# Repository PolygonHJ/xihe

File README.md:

# Xihe
**Xihe** is a self-sustaining, ultra-low-power sensing platform designed for long-lifetime deployments with zero maintenance. Powered by ambient energy sources such as solar or background RF, the system stores energy in supercapacitors until it reaches a threshold sufficient to activate, sense, and transmit data wirelessly. Once depleted, it enters a dormant state and repeats the cycle.

The system is designed to be as small and unobtrusive as possible, enabling it to be placed in an environment, monitor passively, and be forgotten—both visually and in terms of maintenance.

## System Overview
The platform consists of:

### 1. **Main Board — "Xihe-Core"**
- Hosts the energy harvesting and power management circuitry,
- Includes high-capacitance supercapacitor storage,
- Integrates a **Seeed XIAO nRF54L15** module for BLE/Zigbee communication,
- Provides a modular connector interface for sensor boards (I²C, SPI, UART, Analogue),
- Manages energy thresholds and system wakeup logic.

### 2. **Sensor Modules**
- Plug-in sensor boards for flexibility,
- Operate only during active energy windows to minimize load,
- Interchangeable to allow flexibility in deployment.

### 3. **Energy Storage Modules**
- Optional add-ons for extended runtime or energy reserve (Supercapacitors or Batteries),
- Connect to the side or bottom of the board for flexibility,
- Extend active life at the cost of increased physical size.

## Features
- ⚡ **Ambient Energy Harvesting**: Solar (single-cell) supported; RF harvesting planned,
- 🔋 **Supercapacitor-Based Power Storage**: Maintenance-free,
- 📡 **Low-Power Wireless Comms**: BLE/Zigbee-ready for periodic broadcast,
- 🧩 **Modular Sensing**: Swappable sensor boards and energy modules for application-specific deployments,
- 🔄 **Cyclic Operation**: Charge → Activate → Sense → Transmit → Sleep,
- ♻️ **Designed for Longevity**: No batteries, no wires, no maintenance

## Use Cases
The project is intended for low-effort, low-maintenance monitoring in home automation or other low-frequency sensing environments.

Example sensing applications:
- Light  
- Temperature  
- Humidity  
- Moisture  
- Open/Close (e.g. reed switch)  

## Status
The hardware is under active development. No hardware for software has been produced or tested yet.

# Future Ideas
- Energy storage modules,
- RF energy harvesting,
- Modularise harvesting and energy storage sections.

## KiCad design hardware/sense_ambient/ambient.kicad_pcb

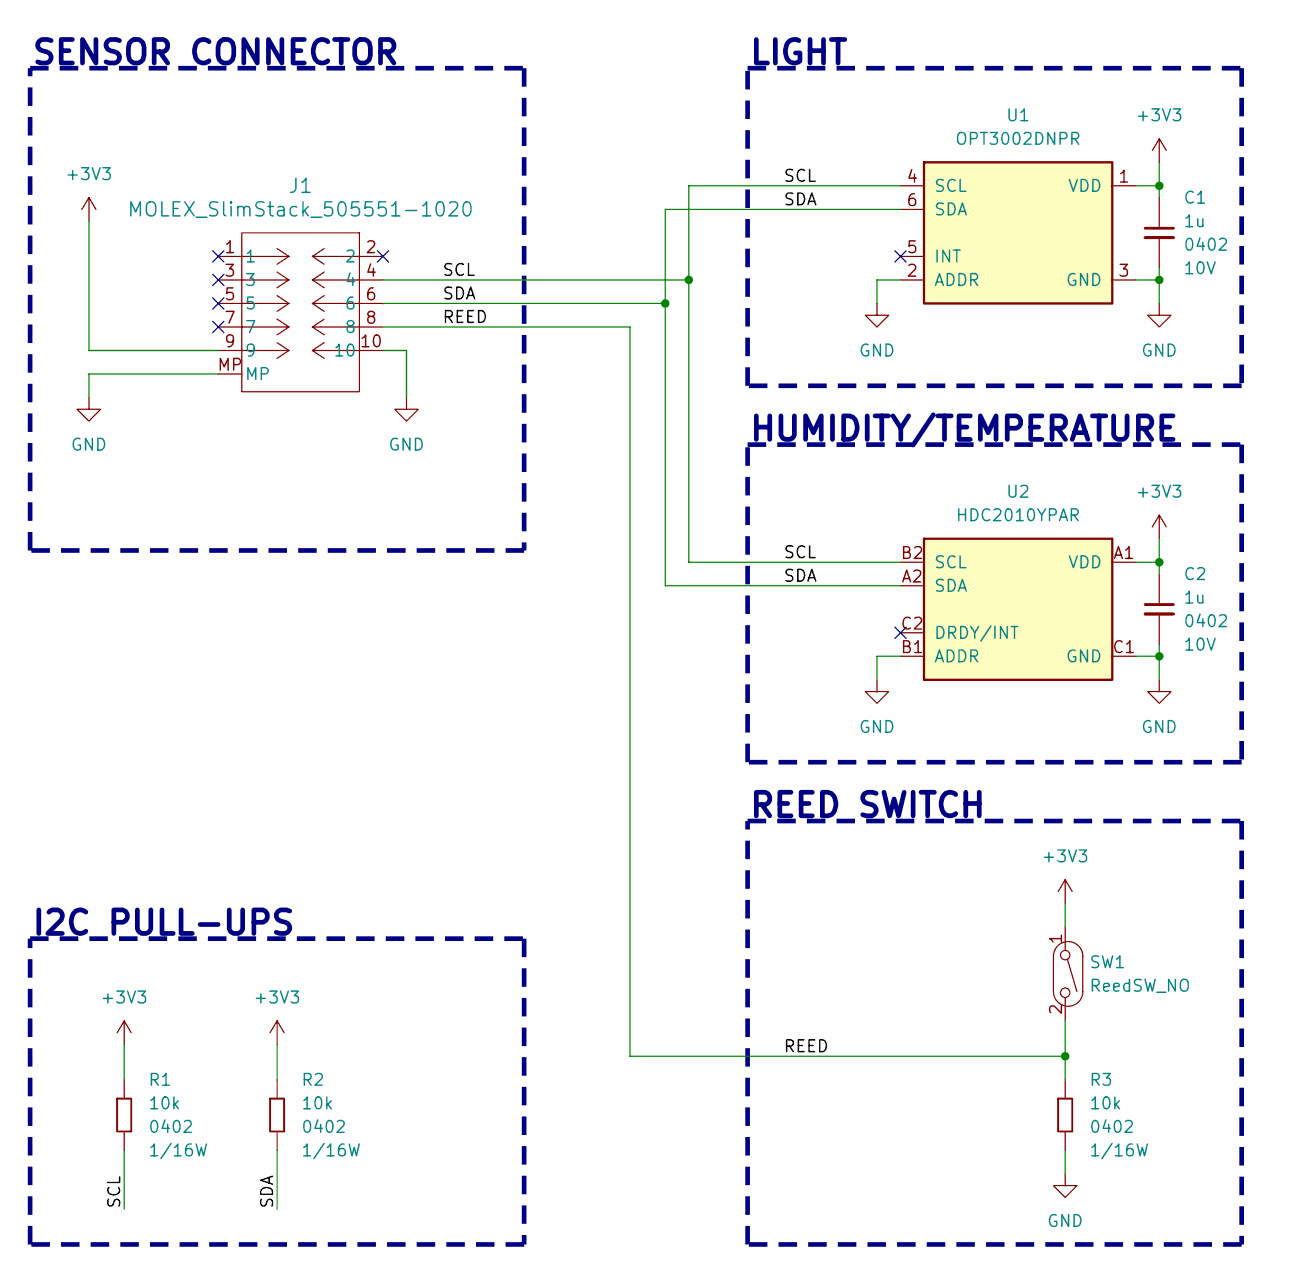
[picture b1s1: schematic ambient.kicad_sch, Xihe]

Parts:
C1, C2: 1u; C_0402_1005Metric; Voltage Rating 10V; Part Number GRM155Z71A105KE01J
J1: MOLEX_SlimStack_505551-1020; Part Number 5055511020
R1, R2, R3: 10k; R_0402_1005Metric; Part Number RC0402FR-0710KP
SW1: ReedSW_NO; COMUS_RI80SMDM0510J1; Part Number RI80SMDM-0510-J1
U1: OPT3002DNPR; TI_6USON_DNP; Part Number OPT3002DNPR
U2: HDC2010YPAR; TI_6DSBGA_YPA; Part Number HDC2010YPAR

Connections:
+3V3: C1.1, C2.1, J1.9, R1.1, R2.1, SW1.1 (A), U1.1 (VDD), U2.A1 (VDD)
/REED: J1.8, R3.1, SW1.2 (B)
/SCL: J1.4, R1.2, U1.4 (SCL), U2.B2 (SCL)
/SDA: J1.6, R2.2, U1.6 (SDA), U2.A2 (SDA)
GND: C1.2, C2.2, J1.10, J1.MP, R3.2, U1.2 (ADDR), U1.3 (GND), U1.7 (GND), U2.B1 (ADDR), U2.C1 (GND)

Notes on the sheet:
REED SWITCH
SENSOR CONNECTOR
I2C PULL-UPS
HUMIDITY/TEMPERATURE
LIGHT

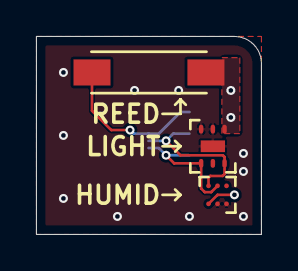
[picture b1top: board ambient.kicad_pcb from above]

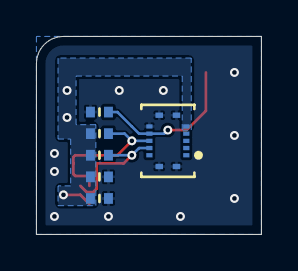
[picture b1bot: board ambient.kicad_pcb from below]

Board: 2 copper layers, 12.5 x 11.0 mm, 9 parts (6 on the bottom side), 5 nets.

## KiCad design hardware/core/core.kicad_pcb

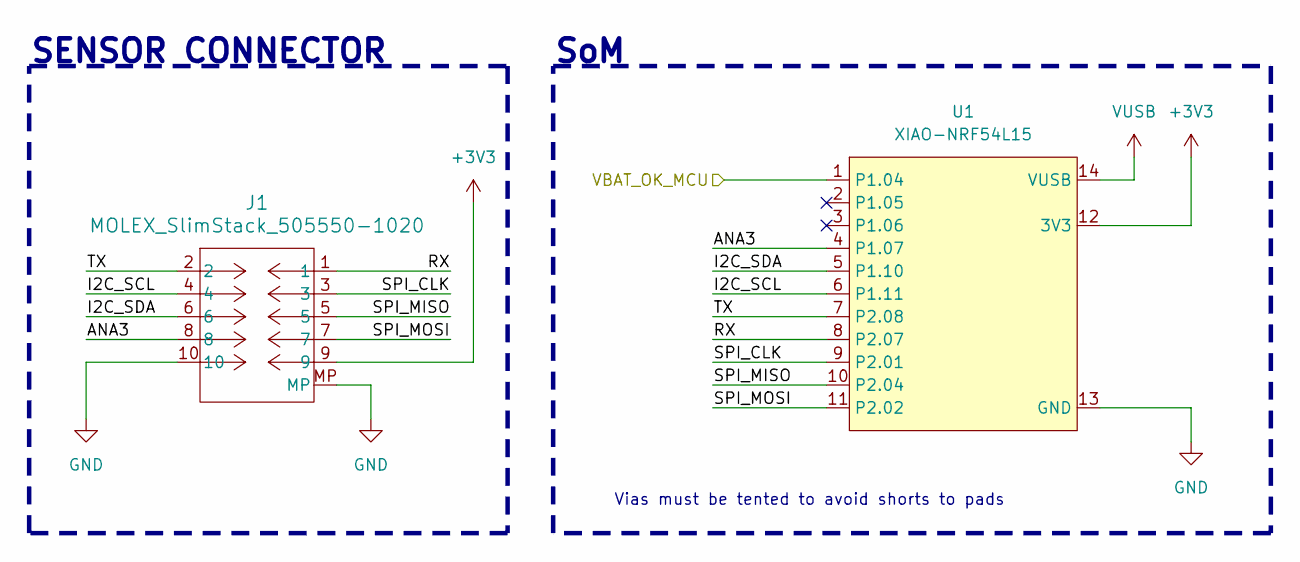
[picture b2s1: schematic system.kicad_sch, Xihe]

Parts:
J1: MOLEX_SlimStack_505550-1020; Part Number 5055501020
U1: XIAO-NRF54L15; XIAO-NRF54L15-DIP; Part Number XIAO-NRF54L15

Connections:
+3V3: J1.9, U1.12 (3V3); also elsewhere on the board
/harvester/VBAT_OK_MCU: U1.1 (P1.04); also elsewhere on the board
/system/ANA3: J1.8, U1.4 (P1.07)
/system/I2C_SCL: J1.4, U1.6 (P1.11)
/system/I2C_SDA: J1.6, U1.5 (P1.10)
/system/RX: J1.1, U1.8 (P2.07)
/system/SPI_CLK: J1.3, U1.9 (P2.01)
/system/SPI_MISO: J1.5, U1.10 (P2.04)
/system/SPI_MOSI: J1.7, U1.11 (P2.02)
/system/TX: J1.2, U1.7 (P2.08)
GND: J1.10, J1.MP, U1.13 (GND); also elsewhere on the board
VUSB: U1.14 (VUSB); also elsewhere on the board

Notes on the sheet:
SoM
SENSOR CONNECTOR
Vias must be tented to avoid shorts to pads

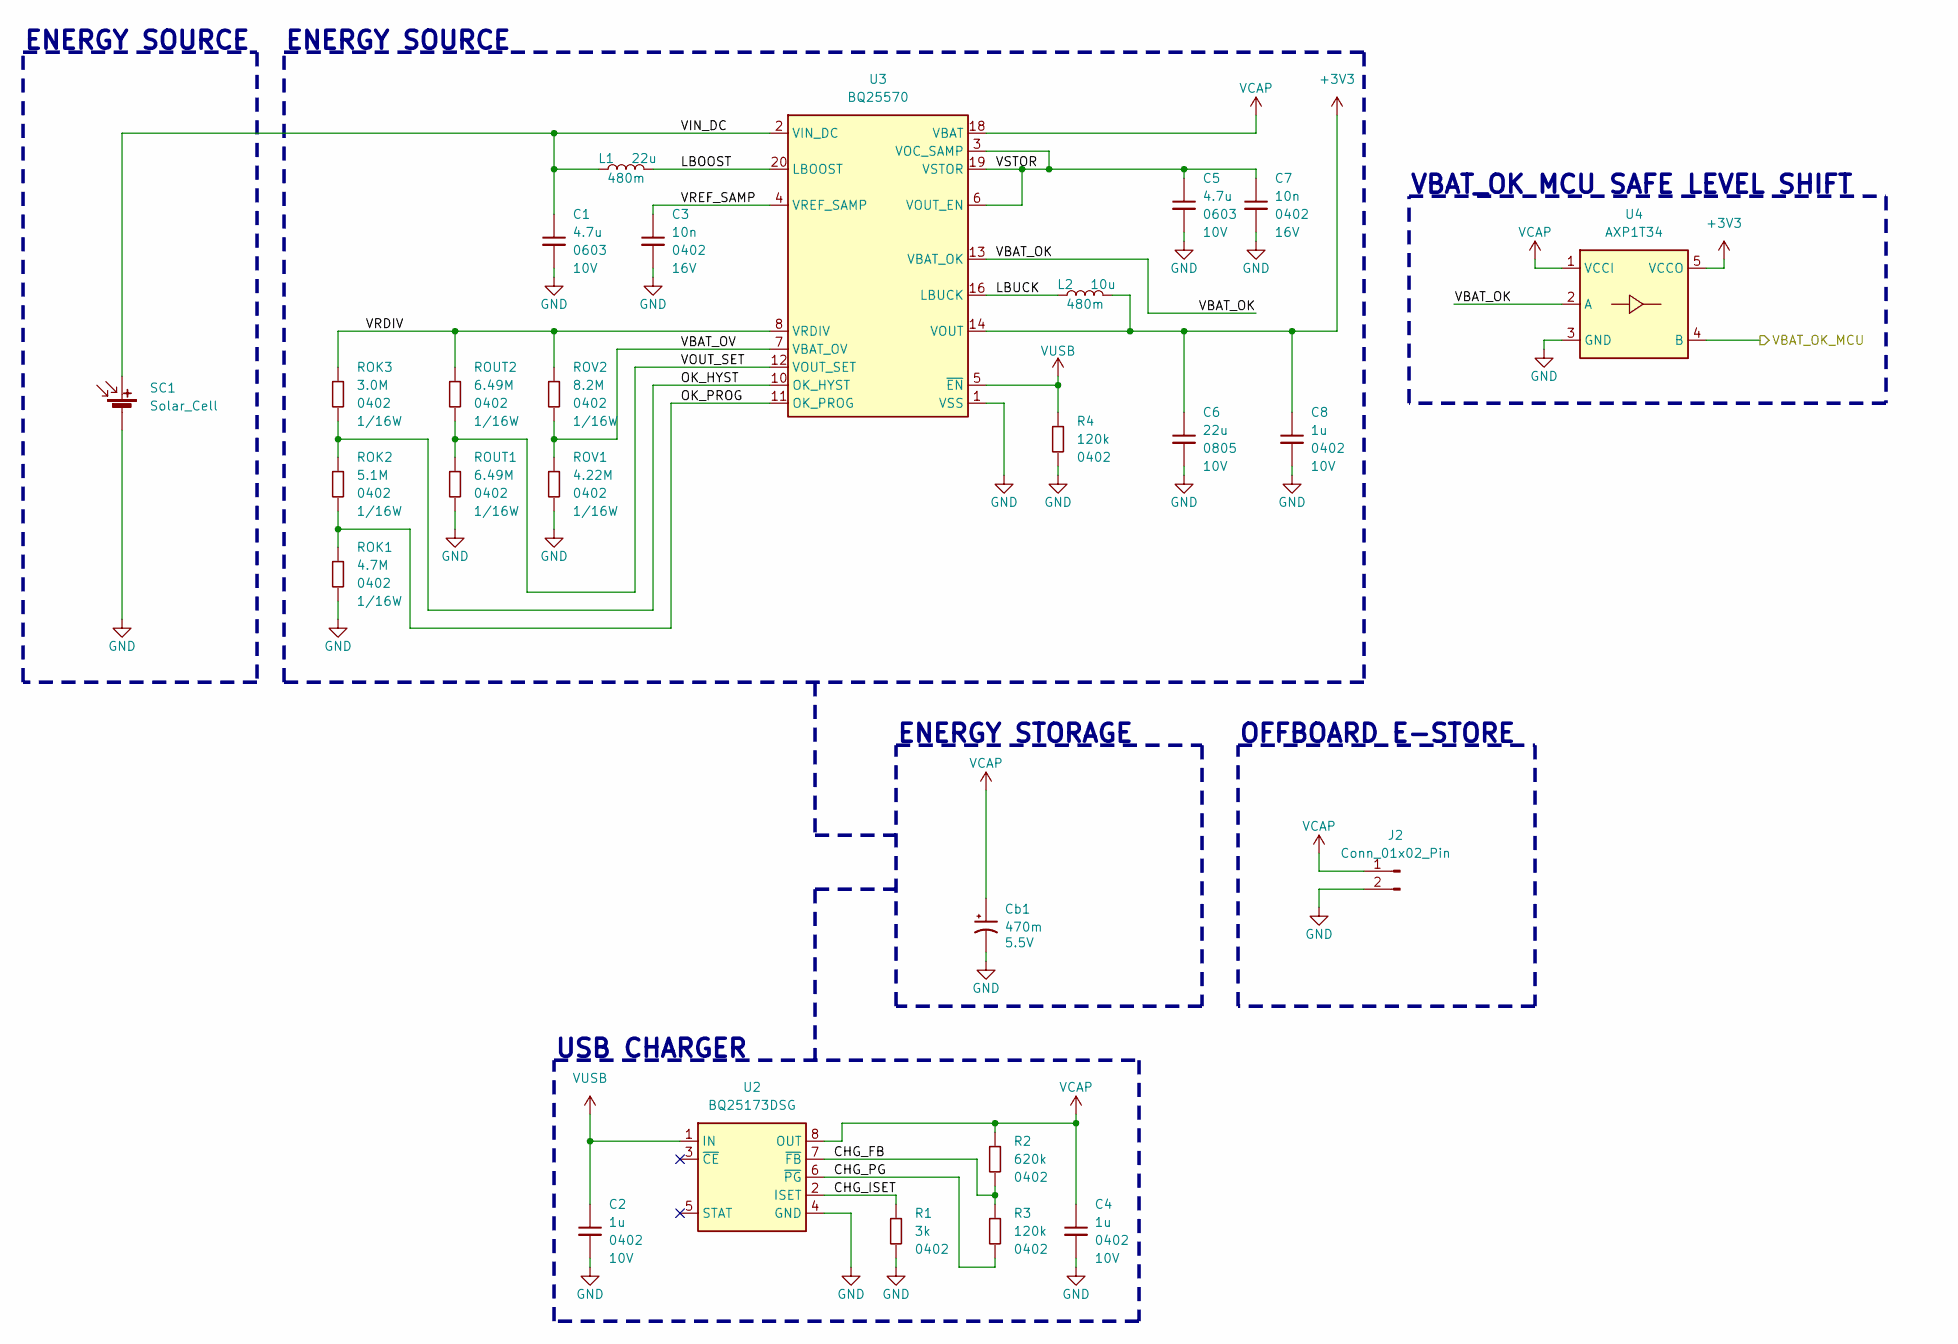
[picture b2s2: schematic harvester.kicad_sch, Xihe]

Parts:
C1, C5: 4.7u; C_0603_1608Metric; Voltage Rating 10V; Part Number GRM188Z71A475ME15D
C2, C4, C8: 1u; C_0402_1005Metric; Voltage Rating 10V; Part Number GRM155Z71A105KE01J
C3, C7: 10n; C_0402_1005Metric; Voltage Rating 16V; Part Number GRM155R71C103KA01D
C6: 22u; C_0805_2012Metric; Voltage Rating 10V; Part Number GRM21BZ71A226ME15L
Cb1: 470m; EATON_KR5R5H474R; Voltage Rating 5.5V; Part Number EDC474Z5R5H
J2: Conn_01x02_Pin; PD_801-83-002-20-001101; Part Number 801-83-002-20-001101
L1: 22u; TY_Inductor_NRS4012; Part Number NRS4012T220MDGJ
L2: 10u; L_1008_2520Metric; Part Number DFE252012F-100M=P2
R1: 3k; R_0402_1005Metric; Part Number RC0402FR-133KL
R2: 620k; R_0402_1005Metric; Part Number RC0402FR-07620KL
R3, R4: 120k; R_0402_1005Metric; Part Number RC0402FR-07120KL
ROK1: 4.7M; R_0402_1005Metric; Part Number RC0402FR-074M7L
ROK2: 5.1M; R_0402_1005Metric; Part Number RC0402FR-075M1L
ROK3: 3.0M; R_0402_1005Metric; Part Number RC0402FR-073ML
ROUT1, ROUT2: 6.49M; R_0402_1005Metric; Part Number RC0402FR-076M49L
ROV1: 4.22M; R_0402_1005Metric; Part Number RC0402FR-074M22L
ROV2: 8.2M; R_0402_1005Metric; Part Number RC0402FR-078M2L
SC1: Solar_Cell; ANYSOLAR_KXOB25; Part Number KXOB25-03X4F-TR
U2: BQ25173DSG; TI_8WSON_DSG; Part Number BQ25173DSGR
U3: BQ25570; TI_20VQFN_RGR; Part Number BQ25570RGRR
U4: AXP1T34; NX_5SOT353; Part Number 74AXP1T34GWH

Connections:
+3V3: C6.1, C8.1, L2.2, U3.14 (VOUT), U4.5 (VCCO); also elsewhere on the board
/harvester/CHG_FB: R2.2, R3.1, U2.7 (~FB)
/harvester/CHG_ISET: R1.1, U2.2 (ISET)
/harvester/CHG_PG: R3.2, U2.6 (~PG)
/harvester/LBOOST: L1.2, U3.20 (LBOOST)
/harvester/LBUCK: L2.1, U3.16 (LBUCK)
/harvester/OK_HYST: ROK2.1, ROK3.2, U3.10 (OK_HYST)
/harvester/OK_PROG: ROK1.1, ROK2.2, U3.11 (OK_PROG)
/harvester/VBAT_OK: U3.13 (VBAT_OK), U4.2 (A)
/harvester/VBAT_OK_MCU: U4.4 (B); also elsewhere on the board
/harvester/VBAT_OV: ROV1.1, ROV2.2, U3.7 (VBAT_OV)
/harvester/VIN_DC: C1.1, L1.1, SC1.1 (+), U3.2 (VIN_DC)
/harvester/VOUT_SET: ROUT1.1, ROUT2.2, U3.12 (VOUT_SET)
/harvester/VRDIV: ROK3.1, ROUT2.1, ROV2.1, U3.8 (VRDIV)
/harvester/VREF_SAMP: C3.1, U3.4 (VREF_SAMP)
/harvester/VSTOR: C5.1, C7.1, U3.3 (VOC_SAMP), U3.6 (VOUT_EN), U3.19 (VSTOR)
GND: C1.2, C2.2, C3.2, C4.2, C5.2, C6.2, C7.2, C8.2, Cb1.2, J2.2, R1.2, R4.2, ROK1.2, ROUT1.2, ROV1.2, SC1.2 (-), U2.4 (GND), U2.9 (GND), U3.1 (VSS), U3.9 (VSS), U3.15 (VSS), U3.17 (VSS), U3.21 (VSS), U4.3 (GND); also elsewhere on the board
VCAP: C4.1, Cb1.1, J2.1, R2.1, U2.8 (OUT), U3.18 (VBAT), U4.1 (VCCI)
VUSB: C2.1, R4.1, U2.1 (IN), U3.5 (~EN); also elsewhere on the board

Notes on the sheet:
VBAT_OK MCU SAFE LEVEL SHIFT
ENERGY STORAGE
OFFBOARD E-STORE
ENERGY SOURCE
USB CHARGER

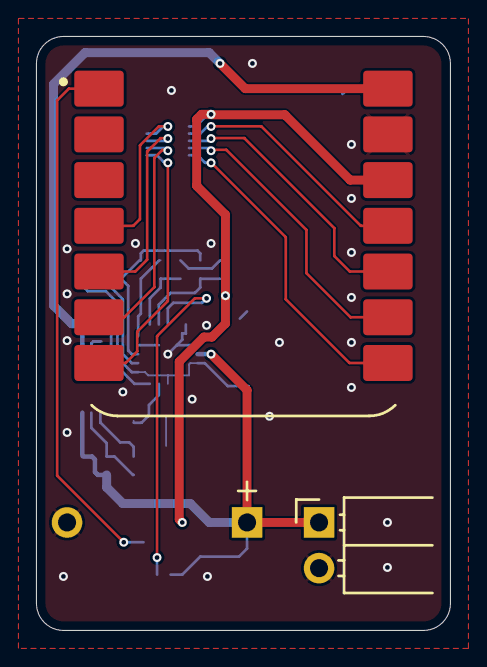
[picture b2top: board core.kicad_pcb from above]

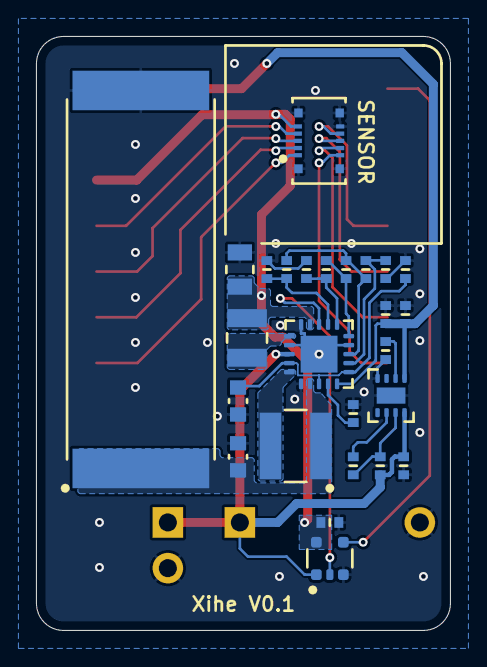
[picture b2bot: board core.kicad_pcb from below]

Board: 2 copper layers, 23.0 x 33.0 mm, 29 parts (26 on the bottom side), 27 nets.

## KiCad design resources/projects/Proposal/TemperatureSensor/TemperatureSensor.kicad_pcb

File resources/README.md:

# Resources

- [Energy Harvester](./energy_harvester/): files related to the energy harvester chip (such as calculations).
- [PcbWay Manufacturing Files](./pcbway_manufacturing_rules/): reference rules file with PcbWays manufacturing capabilities.
- [Projects](./projects/): reference projects and exmaples;
  - [Proposal](./projects/Proposal/) is an initial concept design for a single sided board to test hardware with. This primarily was to test the USB-SWD circuit more easily, but the replacement on this sub-circuit with the Xiao nRF54L15 means the test design is less required.
  - [Xiao nRF54L15 Module](https://wiki.seeedstudio.com/xiao_nrf54l15_sense_getting_started/), an nRF54L15 module from seeed studio used for this project.
  - [BeeLight](https://github.com/Kampi/BeeLight), open source zigbee environment sensor.
  - [Pi Debug Probe](./projects/Pi%20Debugger), onboard USB-SWD schematics and firmware. 
  - [Solar nRF](https://github.com/PocketConcepts/Solar_nRF), low energy harvester example using the BQ25504.

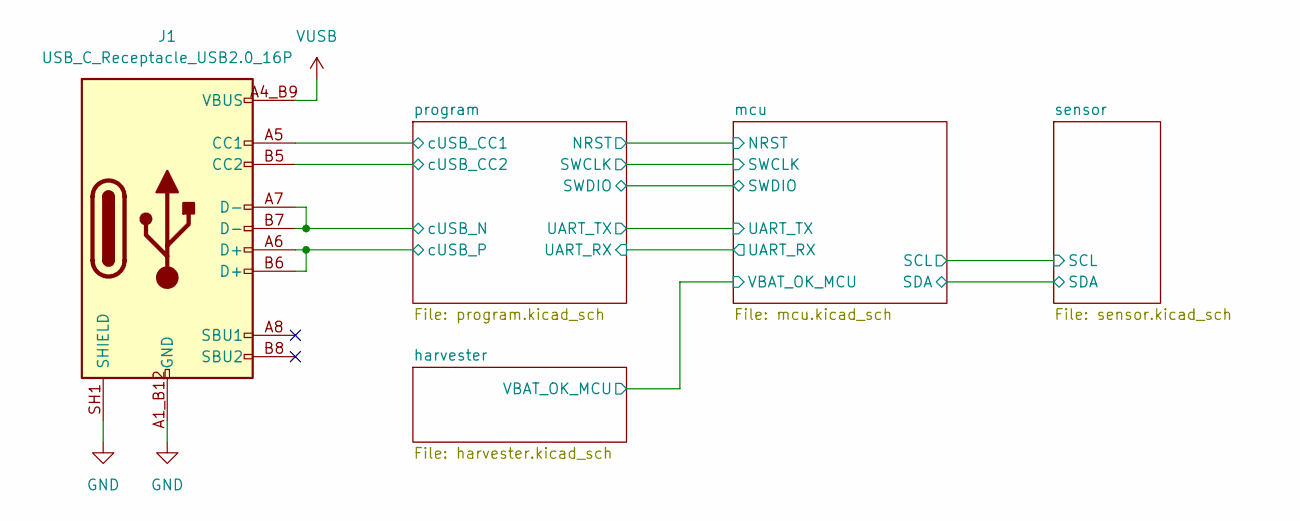
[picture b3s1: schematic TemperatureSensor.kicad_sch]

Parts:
J1: USB_C_Receptacle_USB2.0_16P; GCT_USB4105-GF-A; Part Number USB4105-GF-A

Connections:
/program/cUSB_CC1: J1.A5 (CC1); also elsewhere on the board
/program/cUSB_CC2: J1.B5 (CC2); also elsewhere on the board
/program/cUSB_N: J1.A7 (D-), J1.B7 (D-); also elsewhere on the board
/program/cUSB_P: J1.A6 (D+), J1.B6 (D+); also elsewhere on the board
GND: J1.A1_B12 (GND), J1.B1_A12 (GND), J1.SH1 (SHIELD), J1.SH2 (SHIELD), J1.SH3 (SHIELD), J1.SH4 (SHIELD); also elsewhere on the board
VUSB: J1.A4_B9 (VBUS), J1.B4_A9 (VBUS); also elsewhere on the board

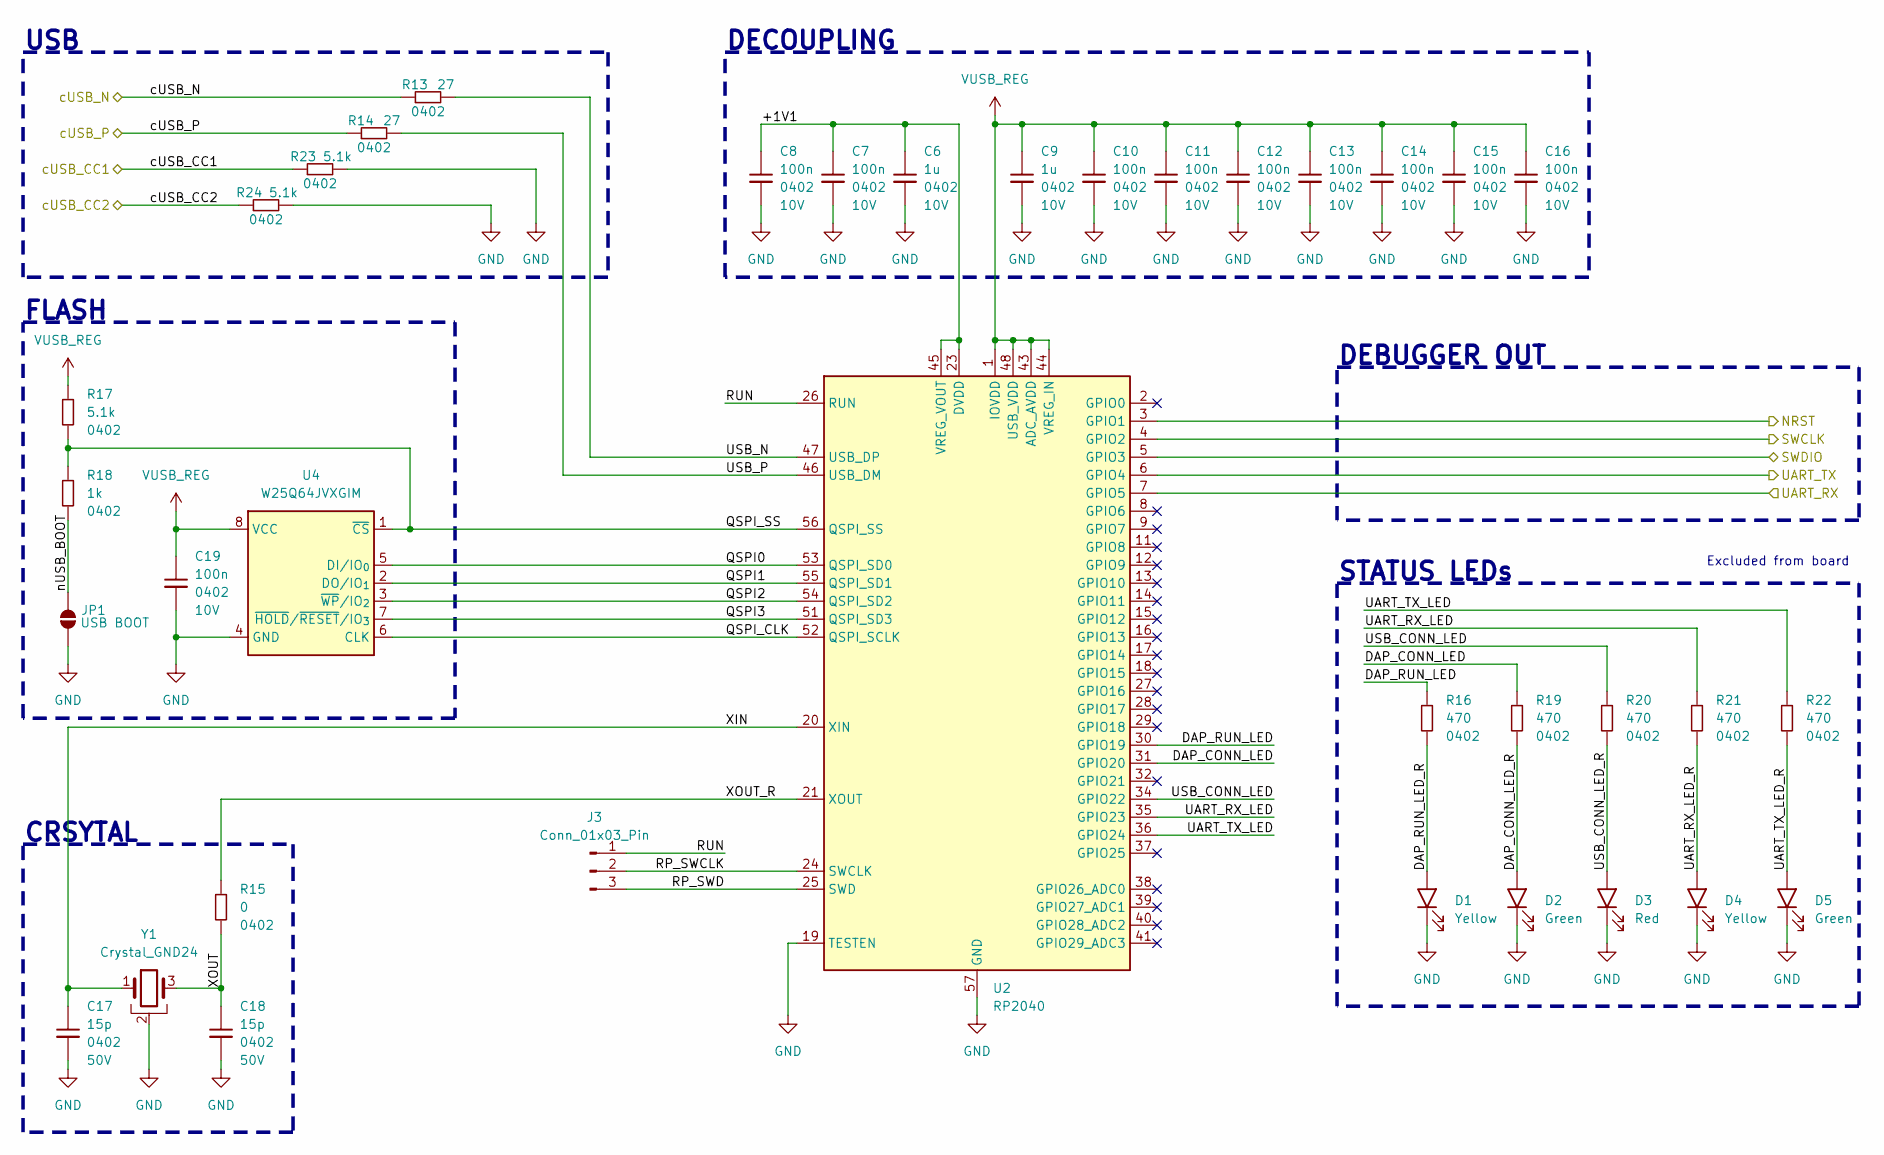
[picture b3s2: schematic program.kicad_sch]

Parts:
C6, C9: 1u; C_0402_1005Metric; Voltage Rating 10V; Part Number GRM155Z71A105KE01J
C7, C8, C10, C11, C12, C13, C14, C15, C16, C19: 100n; C_0402_1005Metric; Voltage Rating 10V; Part Number GRM155R71A104KA01J
C17, C18: 15p; C_0402_1005Metric; Voltage Rating 50V; Part Number GJM1555C1H150GB01D
D1, D4: Yellow; LED_0402_1005Metric
D2, D5: Green; LED_0402_1005Metric
D3: Red; LED_0402_1005Metric
J3: Conn_01x03_Pin; PinHeader_1x03_P2.54mm_Vertical
JP1: SolderJumper_2_Open; SolderJumper2_Open_0402
R13, R14: 27; R_0402_1005Metric; Part Number RC0402FR-0727RL
R15: 0; R_0402_1005Metric; Part Number RC0402FR-070RL
R16, R19, R20, R21, R22: 470; R_0402_1005Metric; Part Number RC0402FR-07470RL
R17, R23, R24: 5.1k; R_0402_1005Metric; Part Number RC0402FR-135K1L
R18: 1k; R_0402_1005Metric; Part Number RC0402FR-131KL
U2: RP2040; QFN-56-1EP_7x7mm_P0.4mm_EP3.2x3.2mm; Part Number SC0914(13)
U4: W25Q64JVXGIM; XSON-8-1EP_4x4mm_P0.8; Part Number W25Q64JVXGIM
Y1: Crystal_GND24; Crystal_SMD_Abracon_ABM8; Part Number ABM8-272-T3

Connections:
/mcu/NRST: U2.3 (GPIO1); also elsewhere on the board
/mcu/SWCLK: U2.4 (GPIO2); also elsewhere on the board
/mcu/SWDIO: U2.5 (GPIO3); also elsewhere on the board
/mcu/UART_RX: U2.7 (GPIO5); also elsewhere on the board
/mcu/UART_TX: U2.6 (GPIO4); also elsewhere on the board
/program/+1V1: C6.1, C7.1, C8.1, U2.23 (DVDD), U2.45 (VREG_VOUT), U2.50 (DVDD)
/program/DAP_CONN_LED: R19.1, U2.31 (GPIO20)
/program/DAP_CONN_LED_R: D2.2 (A), R19.2
/program/DAP_RUN_LED: R16.1, U2.30 (GPIO19)
/program/DAP_RUN_LED_R: D1.2 (A), R16.2
/program/QSPI0: U2.53 (QSPI_SD0), U4.5 (DI/IO_{0})
/program/QSPI1: U2.55 (QSPI_SD1), U4.2 (DO/IO_{1})
/program/QSPI2: U2.54 (QSPI_SD2), U4.3 (~WP/IO_{2})
/program/QSPI3: U2.51 (QSPI_SD3), U4.7 (~HOLD/~RESET/IO_{3})
/program/QSPI_CLK: U2.52 (QSPI_SCLK), U4.6 (CLK)
/program/QSPI_SS: R17.2, R18.1, U2.56 (QSPI_SS), U4.1 (~CS)
/program/RP_SWCLK: J3.2, U2.24 (SWCLK)
/program/RP_SWD: J3.3, U2.25 (SWD)
/program/RUN: J3.1, U2.26 (RUN)
/program/UART_RX_LED: R21.1, U2.35 (GPIO23)
/program/UART_RX_LED_R: D4.2 (A), R21.2
/program/UART_TX_LED: R22.1, U2.36 (GPIO24)
/program/UART_TX_LED_R: D5.2 (A), R22.2
/program/USB_CONN_LED: R20.1, U2.34 (GPIO22)
/program/USB_CONN_LED_R: D3.2 (A), R20.2
/program/USB_N: R13.2, U2.47 (USB_DP)
/program/USB_P: R14.2, U2.46 (USB_DM)
/program/XIN: C17.1, U2.20 (XIN), Y1.1
/program/XOUT: C18.1, R15.2, Y1.3
/program/XOUT_R: R15.1, U2.21 (XOUT)
/program/cUSB_CC1: R23.1; also elsewhere on the board
/program/cUSB_CC2: R24.1; also elsewhere on the board
/program/cUSB_N: R13.1; also elsewhere on the board
/program/cUSB_P: R14.1; also elsewhere on the board
/program/nUSB_BOOT: JP1.2 (B), R18.2
GND: C6.2, C7.2, C8.2, C9.2, C10.2, C11.2, C12.2, C13.2, C14.2, C15.2, C16.2, C17.2, C18.2, C19.2, D1.1 (K), D2.1 (K), D3.1 (K), D4.1 (K), D5.1 (K), JP1.1 (A), R23.2, R24.2, U2.19 (TESTEN), U2.57 (GND), U4.4 (GND), U4.9 (GND), Y1.2, Y1.4; also elsewhere on the board
VUSB_REG: C9.1, C10.1, C11.1, C12.1, C13.1, C14.1, C15.1, C16.1, C19.1, R17.1, U2.1 (IOVDD), U2.10 (IOVDD), U2.22 (IOVDD), U2.33 (IOVDD), U2.42 (IOVDD), U2.43 (ADC_AVDD), U2.44 (VREG_IN), U2.48 (USB_VDD), U2.49 (IOVDD), U4.8 (VCC); also elsewhere on the board

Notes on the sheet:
CRSYTAL
STATUS LEDs
DECOUPLING
FLASH
USB
DEBUGGER OUT
Excluded from board

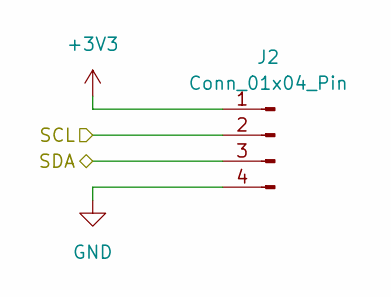
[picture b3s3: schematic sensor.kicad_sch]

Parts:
J2: Conn_01x04_Pin; PinHeader_1x04_P2.54mm_Vertical

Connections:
+3V3: J2.1; also elsewhere on the board
/mcu/SCL: J2.2; also elsewhere on the board
/mcu/SDA: J2.3; also elsewhere on the board
GND: J2.4; also elsewhere on the board

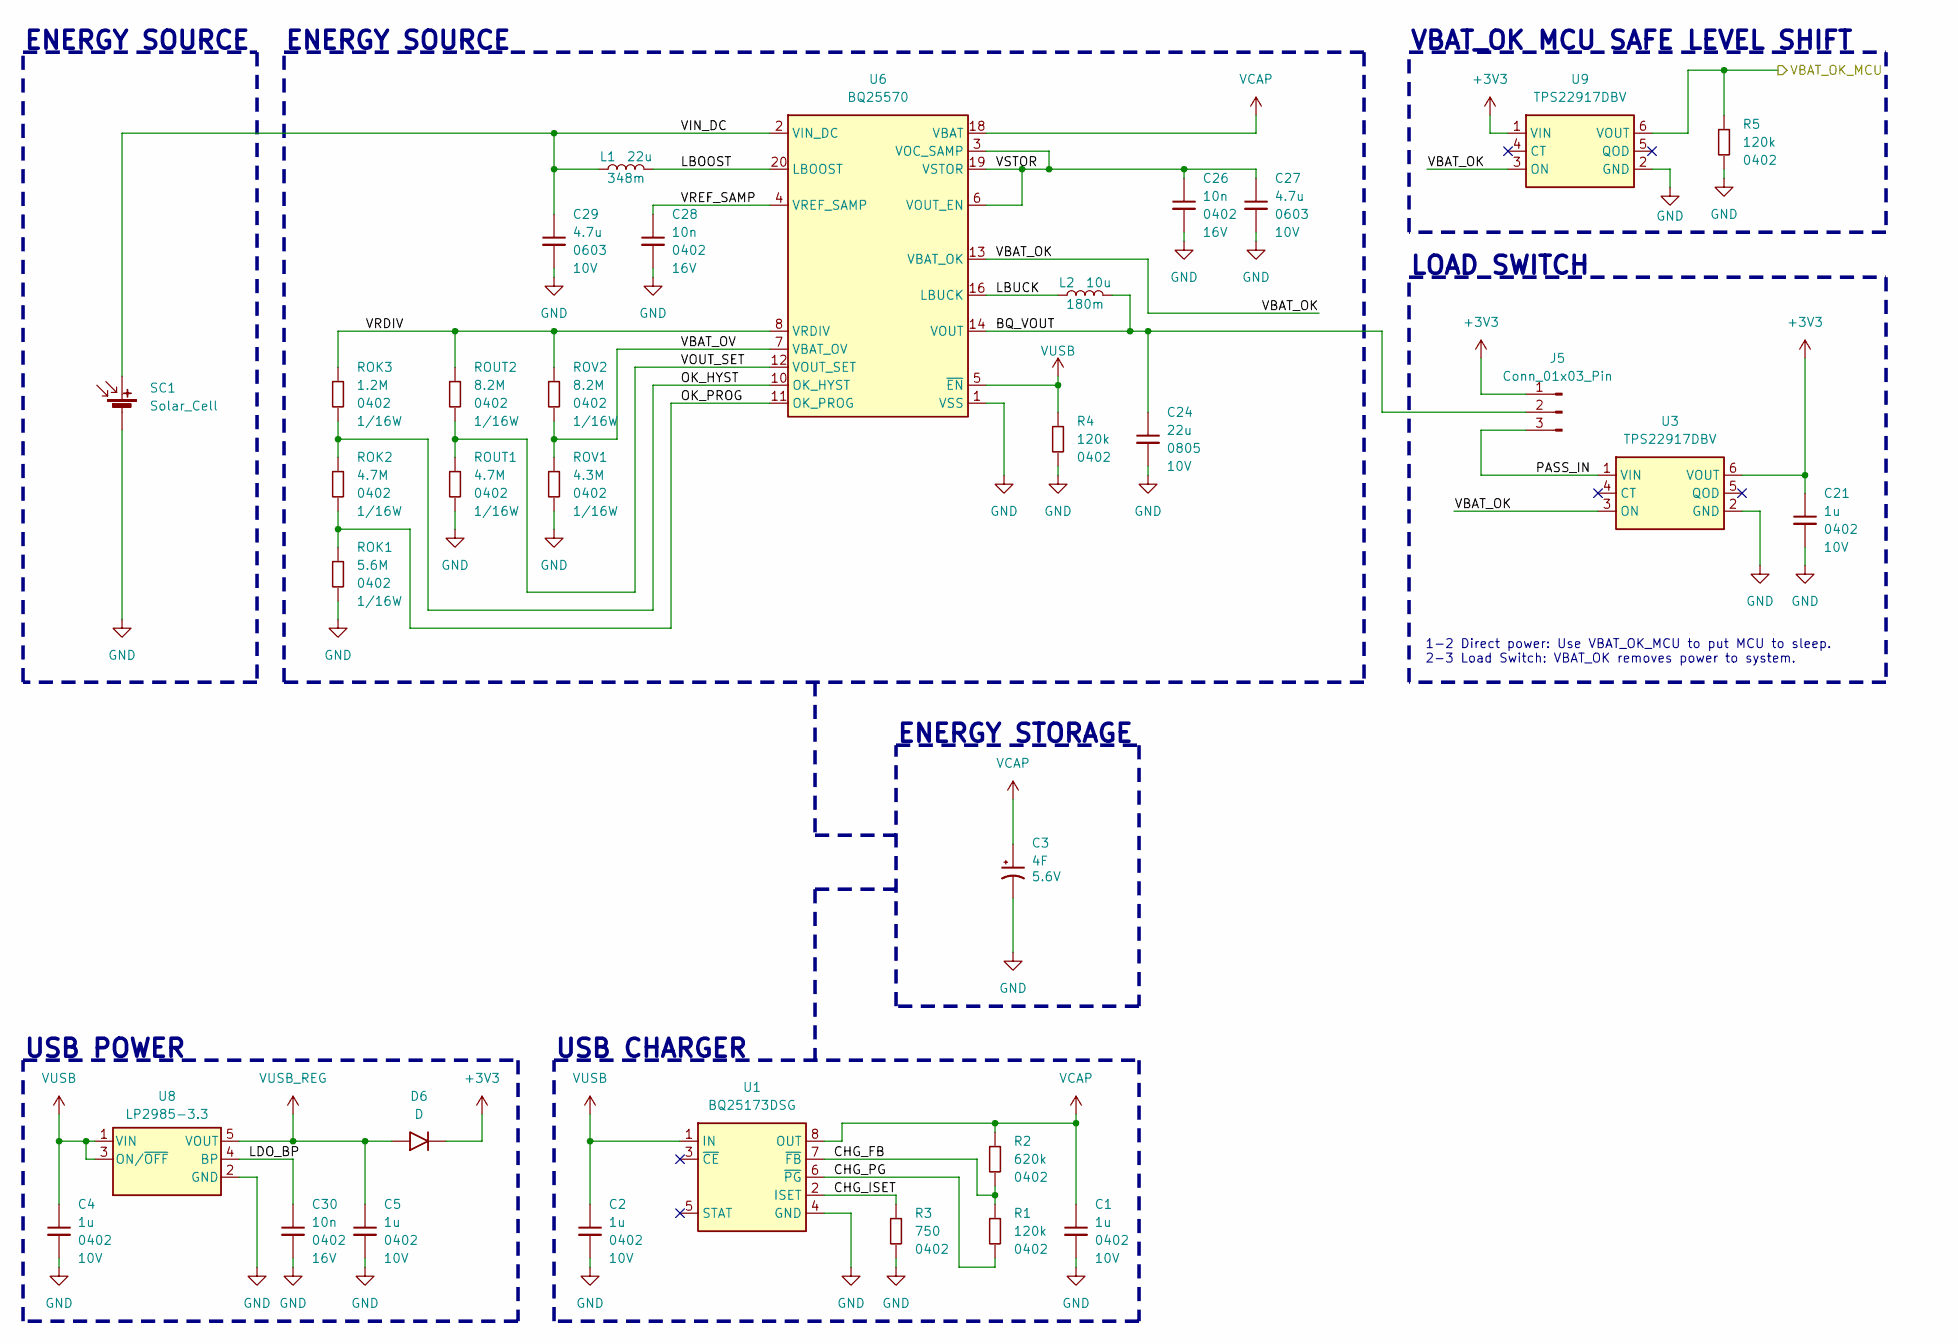
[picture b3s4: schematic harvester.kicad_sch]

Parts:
C1, C2, C4, C5, C21: 1u; C_0402_1005Metric; Voltage Rating 10V; Part Number GRM155Z71A105KE01J
C3: 4F; CAP_MAL219691154E3_VIS; Voltage Rating 5.6V; Part Number MAL219691154E3
C24: 22u; C_0805_2012Metric; Voltage Rating 10V; Part Number GRM21BZ71A226ME15L
C26, C28, C30: 10n; C_0402_1005Metric; Voltage Rating 16V; Part Number GRM155R71C103KA01D
C27, C29: 4.7u; C_0603_1608Metric; Voltage Rating 10V; Part Number GRM188Z71A475ME15D
D6: D; D_SOD-323; Part Number RB751V40,115
J5: Conn_01x03_Pin; PinHeader_1x03_P2.54mm_Vertical
L1: 22u; IND_TAIYO_NRS4018_TAY; Part Number NRS4018T220MDGJ
L2: 10u; IND_TAIYO_NRS4018_TAY; Part Number NRS4018T100MDGJ
R1, R4, R5: 120k; R_0402_1005Metric; Part Number RC0402FR-07120KL
R2: 620k; R_0402_1005Metric; Part Number RC0402FR-07620KL
R3: 750; R_0402_1005Metric; Part Number RC0402FR-13750RL
ROK1: 5.6M; R_0402_1005Metric; Part Number RC0402FR-075M6L
ROK2: 4.7M; R_0402_1005Metric; Part Number RC0402FR-074M7L
ROK3: 1.2M; R_0402_1005Metric; Part Number RC0402FR-071M2L
ROUT1: 4.7M; R_0402_1005Metric; Part Number RC0402FR-074M7L
ROUT2: 8.2M; R_0402_1005Metric; Part Number RC0402FR-078M2L
ROV1: 4.3M; R_0402_1005Metric; Part Number RC0402FR-074M3L
ROV2: 8.2M; R_0402_1005Metric; Part Number RC0402FR-078M2L
SC1: Solar_Cell; KXOB25-05X3F_IXY; Part Number KXOB25-12X1F-TR
U1: BQ25173DSG; WSON-8-1EP_2x2mm_P0.5mm_EP0.9x1.6mm; Part Number BQ25173DSGR
U3, U9: TPS22917DBV; SOT-23-6; Part Number TPS22917DBVR
U6: BQ25570; QFN-20-1EP_3.5x3.5mm_P0.5mm_EP2x2mm; Part Number BQ25570RGRR
U8: LP2985-3.3; SOT-23-5; Part Number LP2985-33DBVR

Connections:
+3V3: C21.1, D6.1 (K), J5.1, U3.6 (VOUT), U9.1 (VIN); also elsewhere on the board
/harvester/BQ_VOUT: C24.1, J5.2, L2.2, U6.14 (VOUT)
/harvester/CHG_FB: R1.1, R2.2, U1.7 (~FB)
/harvester/CHG_ISET: R3.1, U1.2 (ISET)
/harvester/CHG_PG: R1.2, U1.6 (~PG)
/harvester/LBOOST: L1.2, U6.20 (LBOOST)
/harvester/LBUCK: L2.1, U6.16 (LBUCK)
/harvester/LDO_BP: C30.1, U8.4 (BP)
/harvester/OK_HYST: ROK2.1, ROK3.2, U6.10 (OK_HYST)
/harvester/OK_PROG: ROK1.1, ROK2.2, U6.11 (OK_PROG)
/harvester/PASS_IN: J5.3, U3.1 (VIN)
/harvester/VBAT_OK: U3.3 (ON), U6.13 (VBAT_OK), U9.3 (ON)
/harvester/VBAT_OK_MCU: R5.1, U9.6 (VOUT); also elsewhere on the board
/harvester/VBAT_OV: ROV1.1, ROV2.2, U6.7 (VBAT_OV)
/harvester/VIN_DC: C29.1, L1.1, SC1.1 (+), U6.2 (VIN_DC)
/harvester/VOUT_SET: ROUT1.1, ROUT2.2, U6.12 (VOUT_SET)
/harvester/VRDIV: ROK3.1, ROUT2.1, ROV2.1, U6.8 (VRDIV)
/harvester/VREF_SAMP: C28.1, U6.4 (VREF_SAMP)
/harvester/VSTOR: C26.1, C27.1, U6.3 (VOC_SAMP), U6.6 (VOUT_EN), U6.19 (VSTOR)
GND: C1.2, C2.2, C3.2, C4.2, C5.2, C21.2, C24.2, C26.2, C27.2, C28.2, C29.2, C30.2, R3.2, R4.2, R5.2, ROK1.2, ROUT1.2, ROV1.2, SC1.2 (-), U1.4 (GND), U1.9 (GND), U3.2 (GND), U6.1 (VSS), U6.9 (VSS), U6.15 (VSS), U6.17 (VSS), U6.21 (VSS), U8.2 (GND), U9.2 (GND); also elsewhere on the board
VCAP: C1.1, C3.1, R2.1, U1.8 (OUT), U6.18 (VBAT)
VUSB: C2.1, C4.1, R4.1, U1.1 (IN), U6.5 (~EN), U8.1 (VIN), U8.3 (ON/~OFF); also elsewhere on the board
VUSB_REG: C5.1, D6.2 (A), U8.5 (VOUT); also elsewhere on the board

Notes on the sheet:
USB CHARGER
LOAD SWITCH
ENERGY STORAGE
VBAT_OK MCU SAFE LEVEL SHIFT
ENERGY SOURCE
USB POWER
1-2 Direct power: Use VBAT_OK_MCU to put MCU to sleep. 2-3 Load Switch: VBAT_OK removes power to system.

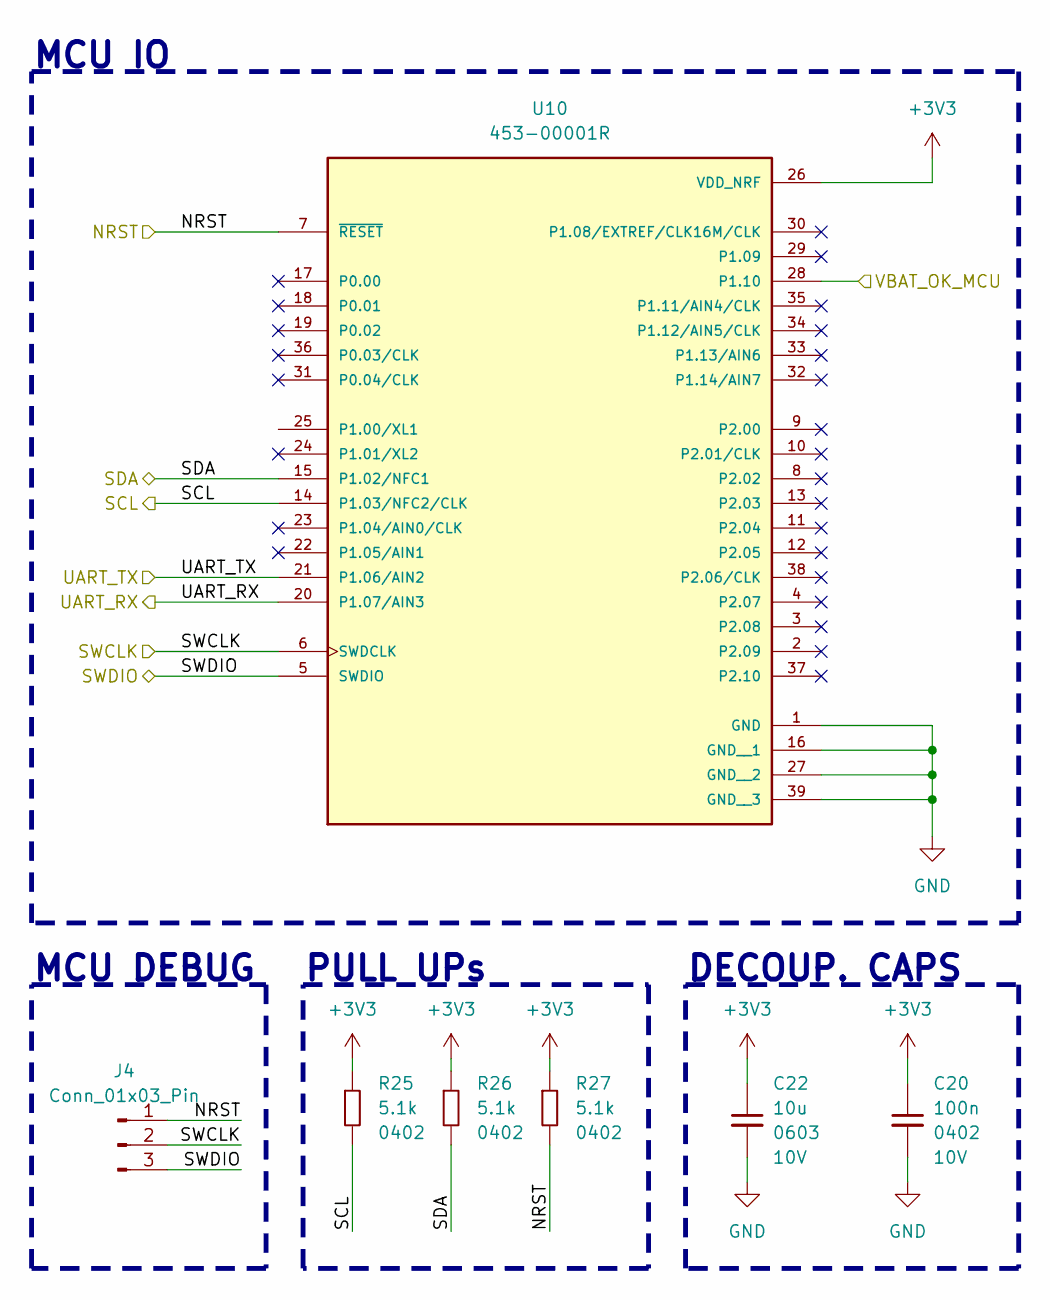
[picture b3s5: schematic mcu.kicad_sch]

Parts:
C20: 100n; C_0402_1005Metric; Voltage Rating 10V; Part Number GRM155R71A104KA01J
C22: 10u; C_0603_1608Metric; Voltage Rating 10V; Part Number GRM188Z71A106KA73D
J4: Conn_01x03_Pin; PinHeader_1x03_P2.54mm_Vertical
R25, R26, R27: 5.1k; R_0402_1005Metric; Part Number RC0402FR-135K1L
U10: 453-00001R; XCVR_453-00001R; PARTREV 1.8

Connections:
+3V3: C20.1, C22.1, R25.1, R26.1, R27.1, U10.26 (VDD_NRF); also elsewhere on the board
/harvester/VBAT_OK_MCU: U10.28 (P1.10); also elsewhere on the board
/mcu/NRST: J4.1, R27.2, U10.7 (~RESET); also elsewhere on the board
/mcu/SCL: R25.2, U10.14 (P1.03/NFC2/CLK); also elsewhere on the board
/mcu/SDA: R26.2, U10.15 (P1.02/NFC1); also elsewhere on the board
/mcu/SWCLK: J4.2, U10.6 (SWDCLK); also elsewhere on the board
/mcu/SWDIO: J4.3, U10.5 (SWDIO); also elsewhere on the board
/mcu/UART_RX: U10.20 (P1.07/AIN3); also elsewhere on the board
/mcu/UART_TX: U10.21 (P1.06/AIN2); also elsewhere on the board
GND: C20.2, C22.2, U10.1 (GND), U10.16 (GND__1), U10.27 (GND__2), U10.39 (GND__3); also elsewhere on the board

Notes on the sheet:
MCU IO
PULL UPs
DECOUP. CAPS
MCU DEBUG

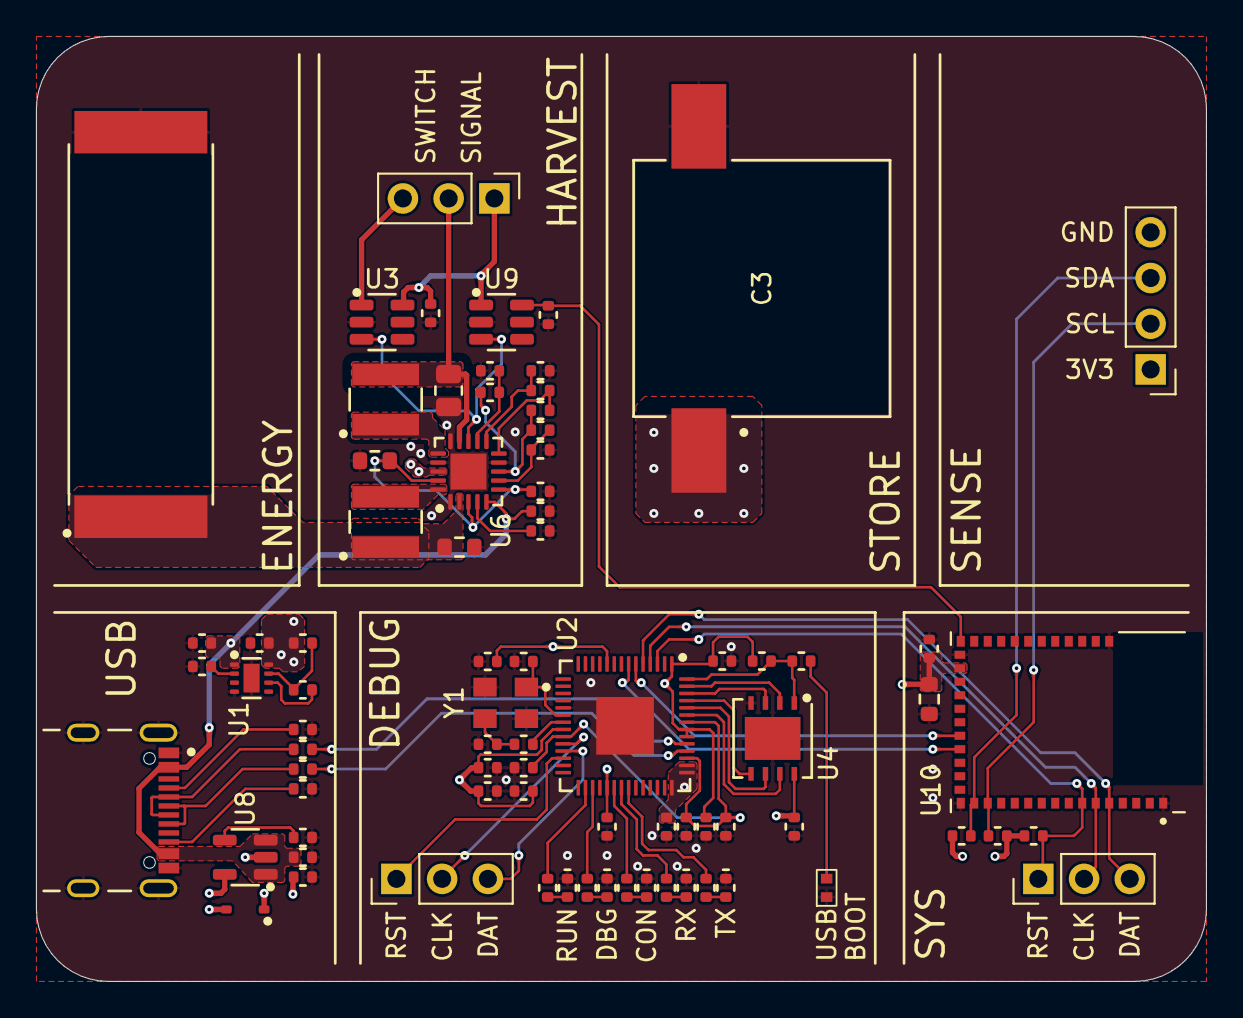
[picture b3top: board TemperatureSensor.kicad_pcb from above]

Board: 4 copper layers, 65.0 x 52.5 mm, 79 parts (0 on the bottom side), 60 nets.
